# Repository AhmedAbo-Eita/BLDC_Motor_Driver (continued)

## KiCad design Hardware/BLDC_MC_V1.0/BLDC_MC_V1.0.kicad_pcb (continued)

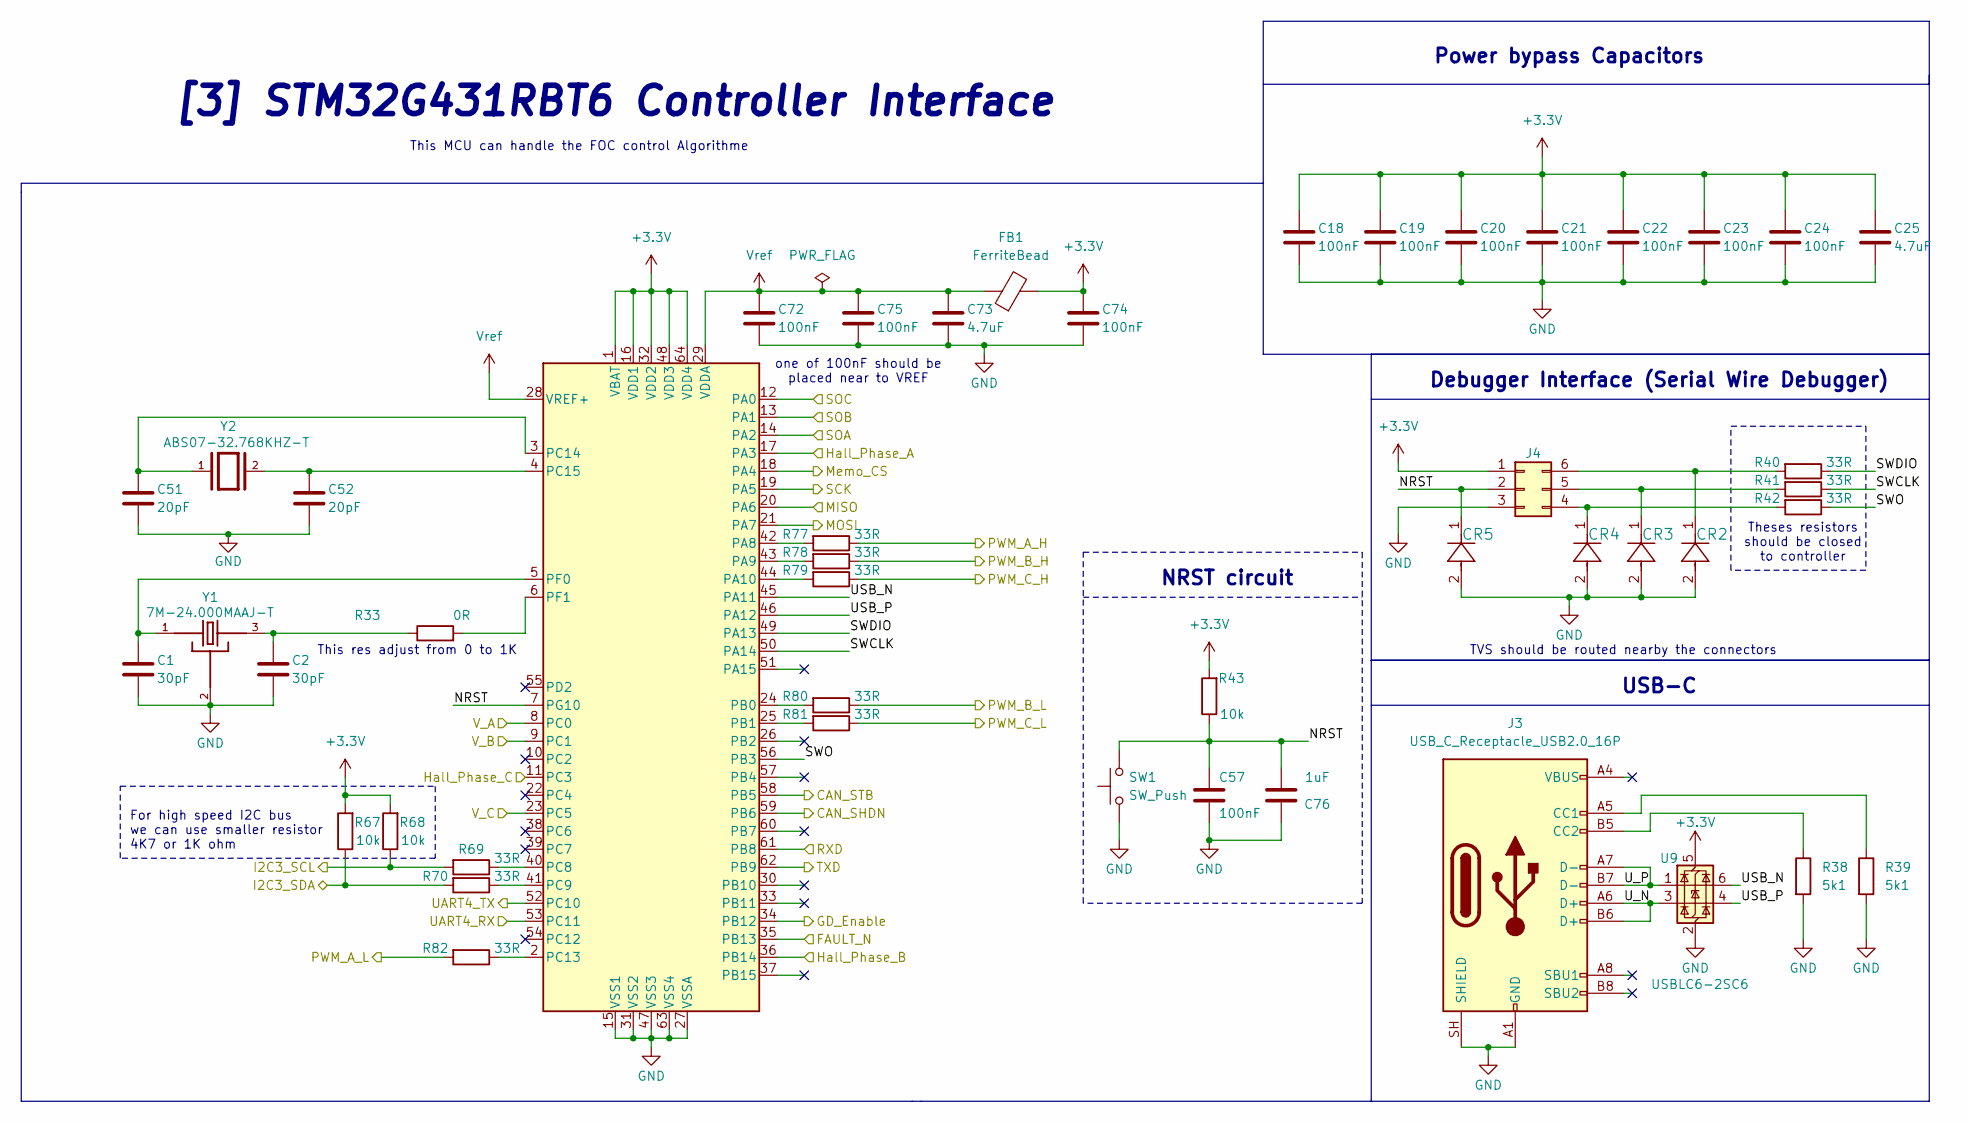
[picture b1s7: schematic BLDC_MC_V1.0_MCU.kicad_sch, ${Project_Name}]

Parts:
C1, C2: 30pF; C_0603_1608Metric; LCSC_PN C113797
C18, C19, C20, C21, C22, C23, C24, C57, C72, C74, C75: 100nF; C_0805_2012Metric; LCSC_PN C28233
C25, C73: 4.7uF; C_1206_3216Metric; LCSC_PN C51205
C51, C52: 20pF; C_0603_1608Metric; LCSC_PN C1648
C76: 1uF; C_0603_1608Metric; LCSC_PN C29936
CR2, CR3, CR4, CR5: PESD3V3L1BA_115; DIODE_PESD3V3L1BA_115_NEX; LCSC_PN C552513
FB1: FerriteBead; L_0603_1608Metric; LCSC_PN C19330
J3: USB_C_Receptacle_USB2.0_16P; USB_C_Receptacle_GCT_USB4105-xx-A_16P_TopMnt_Horizontal
J4: Conn_02x03_Counter_Clockwise; PinHeader_2x03_P2.54mm_Vertical
R33: 0R; R_0603_1608Metric; LCSC_PN C2906974
R38, R39: 5k1; R_0603_1608Metric; LCSC_PN C23186
R40, R41, R42, R69, R70, R77, R78, R79, R80, R81, R82: 33R; R_0603_1608Metric; LCSC_PN C108661
R43: 10k; R_0603_1608Metric; LCSC_PN C98220
R67, R68: 10k; R_0603_1608Metric; LCSC_PN C95204
SW1: SW_Push; SW_Push_1P1T_NO_E-Switch_TL3301NxxxxxG
U4: STM32G431RBT6; LQFP64-10x10mm; LCSC_PN C431633
U9: USBLC6-2SC6; SOT-23-6
Y1: 7M-24.000MAAJ-T; XTAL_7M-24.000MAAJ-T; LCSC_PN C2450233
Y2: ABS07-32.768KHZ-T; XTAL_ABS07-32.768KHZ-T; PARTREV 08.19.15; LCSC_PN C130253

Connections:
+3.3V: C18.1, C19.1, C20.1, C21.1, C22.1, C23.1, C24.1, C25.1, C74.1, FB1.2, J4.1, R43.2, R67.2, R68.2, U4.1 (VBAT), U4.16 (VDD1), U4.32 (VDD2), U4.48 (VDD3), U4.64 (VDD4), U9.5 (VBUS); also elsewhere on the board
/BLDC_MC_V1.0_CAN_Transceiver/CAN_SHDN: U4.59 (PB6); also elsewhere on the board
/BLDC_MC_V1.0_CAN_Transceiver/CAN_STB: U4.58 (PB5); also elsewhere on the board
/BLDC_MC_V1.0_CAN_Transceiver/RXD: U4.61 (PB8); also elsewhere on the board
/BLDC_MC_V1.0_CAN_Transceiver/TXD: U4.62 (PB9); also elsewhere on the board
/BLDC_MC_V1.0_Connectors/I2C3_SCL: R68.1, R69.2; also elsewhere on the board
/BLDC_MC_V1.0_Connectors/I2C3_SDA: R67.1, R70.2; also elsewhere on the board
/BLDC_MC_V1.0_Connectors/UART4_RX: U4.53 (PC11); also elsewhere on the board
/BLDC_MC_V1.0_Connectors/UART4_TX: U4.52 (PC10); also elsewhere on the board
/BLDC_MC_V1.0_Gate_Drive/FAULT_N: U4.35 (PB13); also elsewhere on the board
/BLDC_MC_V1.0_Gate_Drive/GD_Enable: U4.34 (PB12); also elsewhere on the board
/BLDC_MC_V1.0_Gate_Drive/PWM_A_H: R77.1; also elsewhere on the board
/BLDC_MC_V1.0_Gate_Drive/PWM_A_L: R82.2; also elsewhere on the board
/BLDC_MC_V1.0_Gate_Drive/PWM_B_H: R78.1; also elsewhere on the board
/BLDC_MC_V1.0_Gate_Drive/PWM_B_L: R80.1; also elsewhere on the board
/BLDC_MC_V1.0_Gate_Drive/PWM_C_H: R79.1; also elsewhere on the board
/BLDC_MC_V1.0_Gate_Drive/PWM_C_L: R81.1; also elsewhere on the board
/BLDC_MC_V1.0_Gate_Drive/SOA: U4.14 (PA2); also elsewhere on the board
/BLDC_MC_V1.0_Gate_Drive/SOB: U4.13 (PA1); also elsewhere on the board
/BLDC_MC_V1.0_Gate_Drive/SOC: U4.12 (PA0); also elsewhere on the board
/BLDC_MC_V1.0_HallSensor/Hall_Phase_A: U4.17 (PA3); also elsewhere on the board
/BLDC_MC_V1.0_HallSensor/Hall_Phase_B: U4.36 (PB14); also elsewhere on the board
/BLDC_MC_V1.0_HallSensor/Hall_Phase_C: U4.11 (PC3); also elsewhere on the board
/BLDC_MC_V1.0_MCU/MISO: U4.20 (PA6); also elsewhere on the board
/BLDC_MC_V1.0_MCU/MOSI: U4.21 (PA7); also elsewhere on the board
/BLDC_MC_V1.0_MCU/Memo_CS: U4.18 (PA4); also elsewhere on the board
/BLDC_MC_V1.0_MCU/NRST: C57.1, C76.2, CR5.1, J4.2, R43.1, SW1.2, U4.7 (PG10)
/BLDC_MC_V1.0_MCU/SCK: U4.19 (PA5); also elsewhere on the board
/BLDC_MC_V1.0_MCU/SWCLK: R41.1, U4.50 (PA14)
/BLDC_MC_V1.0_MCU/SWDIO: R40.1, U4.49 (PA13)
/BLDC_MC_V1.0_MCU/SWO: R42.1, U4.56 (PB3)
/BLDC_MC_V1.0_MCU/USB_N: U4.45 (PA11), U9.6 (I/O1)
/BLDC_MC_V1.0_MCU/USB_P: U4.46 (PA12), U9.4 (I/O2)
/BLDC_MC_V1.0_MCU/U_N: J3.A6 (D+), J3.B6 (D+), U9.3 (I/O2)
/BLDC_MC_V1.0_MCU/U_P: J3.A7 (D-), J3.B7 (D-), U9.1 (I/O1)
/BLDC_MC_V1.0_MCU/V_A: U4.8 (PC0); also elsewhere on the board
/BLDC_MC_V1.0_MCU/V_B: U4.9 (PC1); also elsewhere on the board
/BLDC_MC_V1.0_MCU/V_C: U4.23 (PC5); also elsewhere on the board
GND: C1.2, C2.2, C18.2, C19.2, C20.2, C21.2, C22.2, C23.2, C24.2, C25.2, C51.2, C52.2, C57.2, C72.2, C73.2, C74.2, C75.2, C76.1, CR2.2, CR3.2, CR4.2, CR5.2, J3.A1 (GND), J3.A12 (GND), J3.SH (SHIELD), J4.3, R38.2, R39.2, SW1.1, U4.15 (VSS1), U4.27 (VSSA), U4.31 (VSS2), U4.47 (VSS3), U4.63 (VSS4), U9.2 (GND), Y1.2, Y1.4; also elsewhere on the board
unnamed: C2.1, R33.1, Y1.3
unnamed: J3.A5 (CC1), R39.1
unnamed: J3.B5 (CC2), R38.1
unnamed: CR4.1, J4.4, R42.2
unnamed: CR3.1, J4.5, R41.2
unnamed: CR2.1, J4.6, R40.2
unnamed: R77.2, U4.42 (PA8)
unnamed: R78.2, U4.43 (PA9)
unnamed: R79.2, U4.44 (PA10)
unnamed: R80.2, U4.24 (PB0)
unnamed: R81.2, U4.25 (PB1)
unnamed: R69.1, U4.40 (PC8)
unnamed: R70.1, U4.41 (PC9)
unnamed: R82.1, U4.2 (PC13)
unnamed: C51.1, U4.3 (PC14), Y2.1
unnamed: C52.1, U4.4 (PC15), Y2.2
unnamed: C1.1, U4.5 (PF0), Y1.1
unnamed: R33.2, U4.6 (PF1)
Vref: C72.1, C73.1, C75.1, FB1.1, U4.28 (VREF+), U4.29 (VDDA); also elsewhere on the board

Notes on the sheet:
Power bypass Capacitors
TVS should be routed nearby the connectors
[3] STM32G431RBT6 Controller Interface
NRST circuit
For high speed I2C bus we can use smaller resistor 4K7 or 1K ohm
Debugger Interface (Serial Wire Debugger)
USB-C
Theses resistors should be closed to controller
This res adjust from 0 to 1K
This MCU can handle the FOC control Algorithme
one of 100nF should be placed near to VREF

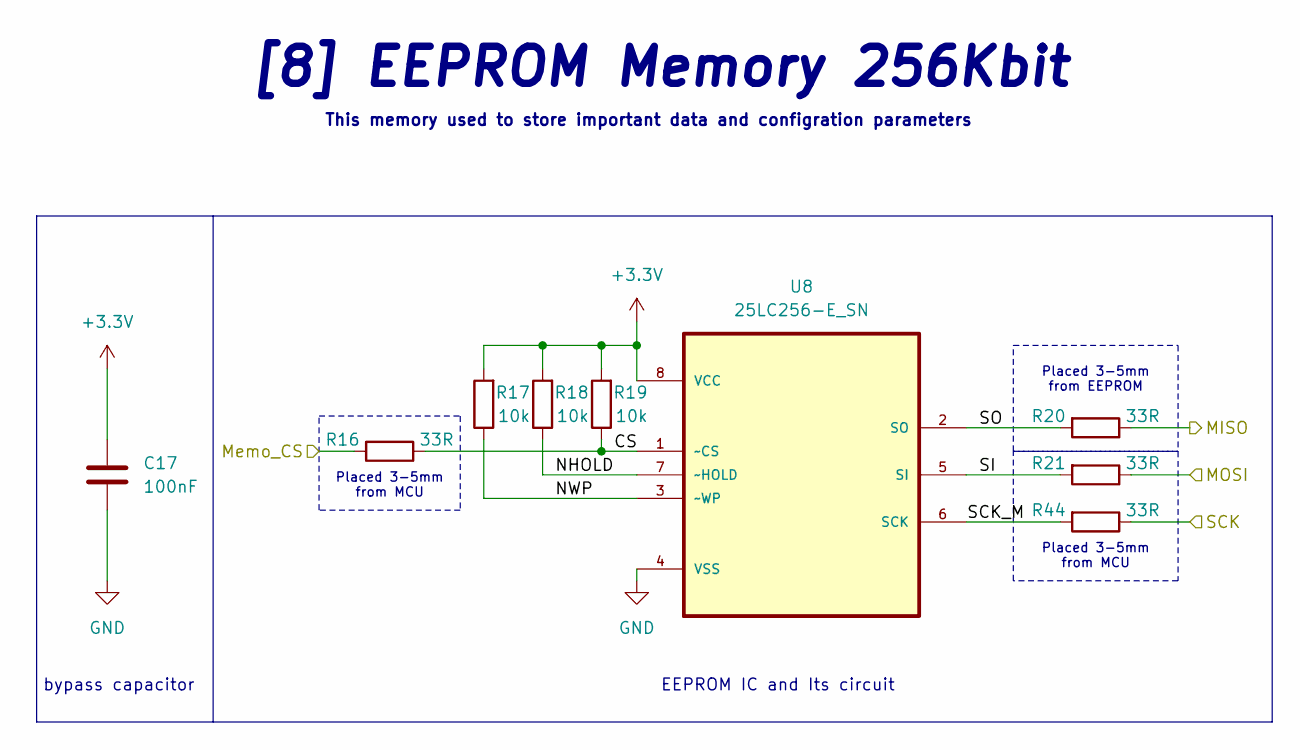
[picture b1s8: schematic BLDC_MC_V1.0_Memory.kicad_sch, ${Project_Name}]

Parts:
C17: 100nF; C_0805_2012Metric; LCSC_PN C28233
R16, R20, R21, R44: 33R; R_0603_1608Metric; LCSC_PN C108661
R17, R18, R19: 10k; R_0603_1608Metric; LCSC_PN C95204
U8: 25LC256-E_SN; SOIC127P599X175-8N; MPN 25LC256-E/SN; LCSC_PN C1349834

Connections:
+3.3V: C17.1, R17.2, R18.2, R19.2, U8.8 (VCC); also elsewhere on the board
/BLDC_MC_V1.0_MCU/MISO: R20.1; also elsewhere on the board
/BLDC_MC_V1.0_MCU/MOSI: R21.1; also elsewhere on the board
/BLDC_MC_V1.0_MCU/Memo_CS: R16.2; also elsewhere on the board
/BLDC_MC_V1.0_MCU/SCK: R44.1; also elsewhere on the board
/BLDC_MC_V1.0_Memory/CS: R16.1, R19.1, U8.1 (~CS)
/BLDC_MC_V1.0_Memory/NHOLD: R18.1, U8.7 (~HOLD)
/BLDC_MC_V1.0_Memory/NWP: R17.1, U8.3 (~WP)
/BLDC_MC_V1.0_Memory/SCK_M: R44.2, U8.6 (SCK)
/BLDC_MC_V1.0_Memory/SI: R21.2, U8.5 (SI)
/BLDC_MC_V1.0_Memory/SO: R20.2, U8.2 (SO)
GND: C17.2, U8.4 (VSS); also elsewhere on the board

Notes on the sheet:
Placed 3-5mm from EEPROM
Placed 3-5mm from MCU
EEPROM IC and Its circuit
This memory used to store important data and configration parameters
bypass capacitor
[8] EEPROM Memory 256Kbit

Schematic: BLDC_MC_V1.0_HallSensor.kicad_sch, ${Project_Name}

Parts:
C58, C59, C60: C; C_0603_1608Metric
C61, C62, C63: 100nF; C_0805_2012Metric; LCSC_PN C28233
R15, R49, R52: 10k; R_0603_1608Metric; LCSC_PN C95204
R45, R47, R50: 18K; R_0603_1608Metric; LCSC_PN C309650
R46, R48, R51: 30K; R_0603_1608Metric; LCSC_PN C723585
U3, U10, U11: TLV9061IDBVR; SOT95P280X145-5N; LCSC_PN C398358

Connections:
+3.3V: C61.1, C62.1, C63.1, U3.5 (V+), U10.5 (V+), U11.5 (V+); also elsewhere on the board
/BLDC_MC_V1.0_Connectors/Hall_A: R45.2; also elsewhere on the board
/BLDC_MC_V1.0_Connectors/Hall_B: R47.2; also elsewhere on the board
/BLDC_MC_V1.0_Connectors/Hall_C: R50.2; also elsewhere on the board
/BLDC_MC_V1.0_HallSensor/Hall_Phase_A: U3.1 (OUT), U3.4 (IN-); also elsewhere on the board
/BLDC_MC_V1.0_HallSensor/Hall_Phase_B: U10.1 (OUT), U10.4 (IN-); also elsewhere on the board
/BLDC_MC_V1.0_HallSensor/Hall_Phase_C: U11.1 (OUT), U11.4 (IN-); also elsewhere on the board
GND: C58.2, C59.2, C60.2, C61.2, C62.2, C63.2, R46.2, R48.2, R51.2, U3.2 (V-), U10.2 (V-), U11.2 (V-); also elsewhere on the board
unnamed: C58.1, R15.1, R45.1, R46.1
unnamed: C59.1, R47.1, R48.1, R49.1
unnamed: C60.1, R50.1, R51.1, R52.1
unnamed: R15.2, U3.3 (IN+)
unnamed: R49.2, U10.3 (IN+)
unnamed: R52.2, U11.3 (IN+)

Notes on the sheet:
For filtering the signal Limiting the input current
[6] Hall Effect Sensor Interface
+3.125V
Drop down the voltage from 5 to 3.3V
For the 3 Phases of Hall Sensor
Buffer OpAmp

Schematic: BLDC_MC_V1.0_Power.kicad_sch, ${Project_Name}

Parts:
C3, C4, C7, C8, C31, C35, C54, C89, C90: 100nF; C_0805_2012Metric; LCSC_PN C28233
C5, C6, C26, C27: 47uF; C_1206_3216Metric; LCSC_PN C403725
C9, C10, C29, C30: 47uF; CP_Elec_10x10.5; LCSC_PN C46528101
C14: 10nF; C_1206_3216Metric; LCSC_PN C377055
C28: 10pF; C_0603_1608Metric; LCSC_PN C1634
C32: 470nF; C_0805_2012Metric; LCSC_PN C13967
C33: 10nF; C_0603_1608Metric; LCSC_PN C100042
C34: 2.2uF; C_0603_1608Metric; LCSC_PN C415535
C36, C53: 1uF; C_0805_2012Metric; LCSC_PN C28323
C37, C55, C56: 4.7uF; C_1206_3216Metric; LCSC_PN C51205
CR10: SMDJ110CA; SMDJSeries_LTF; LCSC_PN C2990268
D1, D2, D3, D4: LED; LED_0603_1608Metric; LCSC_PN C19171390
H1, H2, H3, H4: MountingHole_Pad; MountingHole_2.2mm_M2_Pad_Via
L1: 10uH; L_KOHERelec_MDA7030; LCSC_PN C149584
NT4: NetTie_2; NetTie-2_SMD_Pad2.0mm
Q7: BSC027N10NS5ATMA1; PG-TSON-8-3_INF; PARTREV 2.1; LCSC_PN C534315
R1, R2: 100K; R_0603_1608Metric; LCSC_PN C122538
R3, R6: 0R; R_0603_1608Metric; LCSC_PN C2906974
R4: 9.09K; R_0603_1608Metric; LCSC_PN C844591
R5, R34, R37: 10k; R_0603_1608Metric; LCSC_PN C98220
R9: 1MR; R_1206_3216Metric; LCSC_PN C2907441
R35, R36: 3k3; R_0603_1608Metric; LCSC_PN C22978
U1: LM76005RNPR; QFN50P600X400X80-31N; PARTREV A; LCSC_PN TI LM76005RNPR
U5: LDL1117S33R; SOT230P700X180-4N; PARTREV 7; LCSC_PN C435835
U7: NCV4274ADT50RKG; DPAK-3_ONS; LCSC_PN C233416
U16: LM74700QDRQ1; SOIC8_D_TEX; LCSC_PN C33579657

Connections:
+3.3V: C35.1, C37.1, R36.1, U5.2 (VOUT), U5.4 (VOUT); also elsewhere on the board
+5V: C55.1, C56.1, R35.1, U7.3 (Q); also elsewhere on the board
+12V: C3.1, C4.1, C5.2, C6.2, C26.2, C27.2, C28.1, C36.1, C53.1, C54.1, L1.2, R2.1, R5.2, R6.2, R34.1, U5.3 (VIN), U7.1 (I); also elsewhere on the board
/BLDC_MC_V1.0_Connectors/Vin_DC: C89.1, C90.1, CR10.1, Q7.5, Q7.6, Q7.7, Q7.8, U16.2 (EN), U16.5 (ANODE); also elsewhere on the board
/BLDC_MC_V1.0_Power/Buck_SW: C32.1, L1.1, U1.1 (SW), U1.2 (SW), U1.3 (SW), U1.4 (SW), U1.5 (SW)
/BLDC_MC_V1.0_Power/VCC_Buck: C34.1, U1.8 (VCC)
/BLDC_MC_V1.0_Power/chassis_ground: C14.1, H1.1 (1_1), H2.1 (1_1), H3.1 (1_1), H4.1 (1_1), R9.1
AGND: C31.2, C33.2, C34.2, NT4.2, R1.2, R3.2, R4.2, U1.13 (AGND), U1.14 (AGND), U1.15 (AGND), U1.19 (NC), U1.27 (NC), U1.28 (NC), U1.29 (NC), U1.30 (NC)
GND: C3.2, C4.2, C5.1, C6.1, C7.2, C8.2, C9.2, C10.2, C14.2, C26.1, C27.1, C29.2, C30.2, C35.2, C36.2, C37.2, C53.2, C54.2, C55.2, C56.2, C90.2, CR10.2, D1.1 (K), D2.1 (K), D3.1 (K), D4.1 (K), NT4.1, R9.2, U1.24 (GND), U1.25 (GND), U1.26 (GND), U1.31 (EP), U5.1 (GND), U7.2 (GND), U16.1 (GND); also elsewhere on the board
unnamed: D1.2 (A), R37.2
unnamed: D2.2 (A), R34.2
unnamed: D3.2 (A), R35.2
unnamed: D4.2 (A), R36.2
unnamed: C31.1, R6.1, U1.9 (BIAS)
unnamed: C32.2, U1.6 (BOOT)
unnamed: C28.2, R2.2, R4.1, U1.12 (FB)
unnamed: R5.1, U1.16 (PGOOD)
unnamed: R1.1, U1.10 (RT)
unnamed: C33.1, U1.11 (SS/TRK)
unnamed: R3.1, U1.17 (SYNC/MODE)
unnamed: Q7.4, U16.6 (GATE)
unnamed: U16.3 (N.C), U16.7 (N.C)
unnamed: C89.2, U16.4 (VCAP)
Vin: C7.1, C8.1, C9.1, C10.1, C29.1, C30.1, Q7.1, Q7.2, Q7.3, R37.1, U1.18 (EN), U1.20 (PVIN), U1.21 (PVIN), U1.22 (PVIN), U16.8 (CATHODE); also elsewhere on the board

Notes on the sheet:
Input Cap Bank
Output Cap Bank
The maximum input votage of this 60V so we can use for BLDC motors up to 60V
LDO Fixed out 5V
Indication Leds
Buck IC Circuit
input Capacitor Bank To make the input power pure DC
LDO Fixed out 3.3V
Input PWR Protection
Replaced by 0R
[1] Power Conversion Vin to 12V and 5V to 3.3V
Output Capacitor Bank Recommended from IC datasheet Cout = 150uf Referance design puts 5 of 47uf

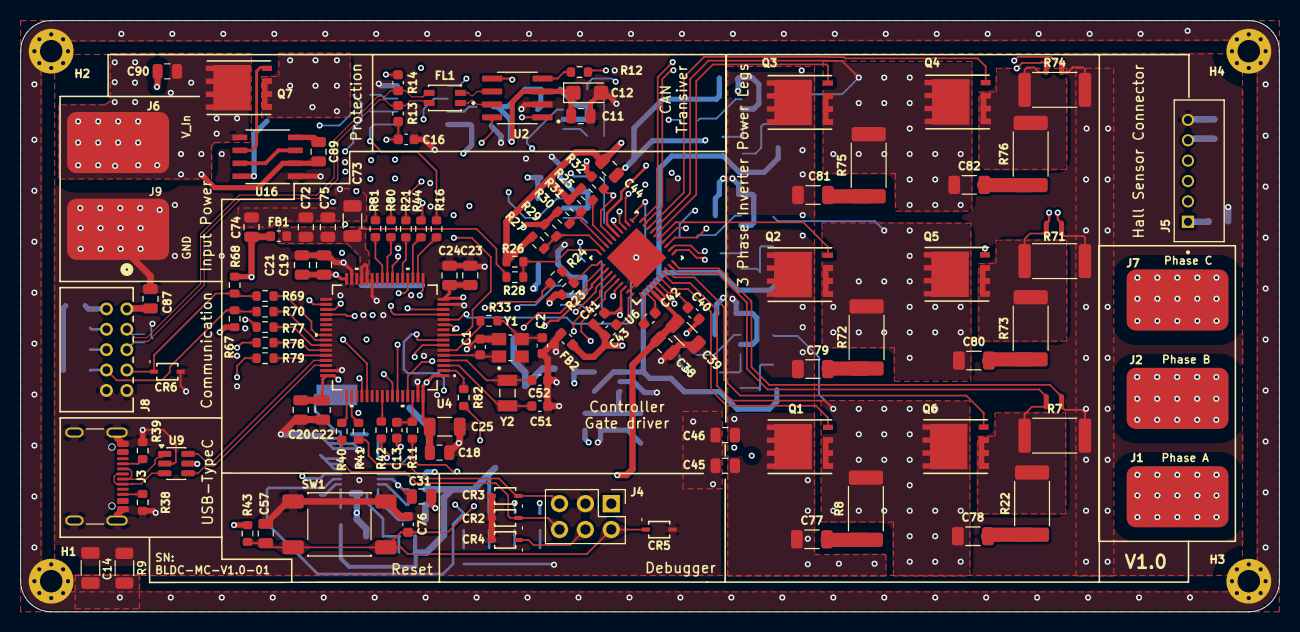
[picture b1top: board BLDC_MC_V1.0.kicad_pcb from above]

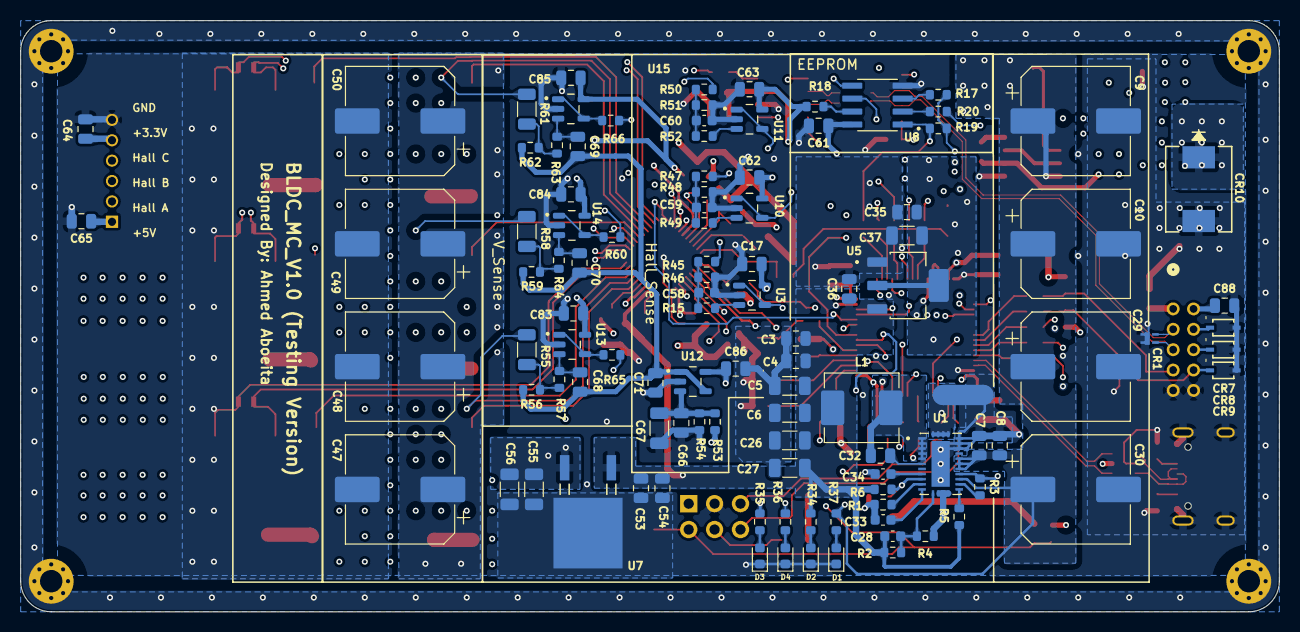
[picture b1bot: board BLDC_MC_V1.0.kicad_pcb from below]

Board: 8 copper layers, 123.5 x 58.0 mm, 234 parts (106 on the bottom side), 148 nets.

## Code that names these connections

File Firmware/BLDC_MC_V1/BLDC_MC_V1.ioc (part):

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Mcu.Name=STM32G431R(6-8-B)Tx
Mcu.Package=LQFP64
Mcu.UserName=STM32G431RBTx
PA0.Mode=IN1-Single-Ended
PA0.Signal=ADC1_IN1
PA1.Mode=IN2-Single-Ended
PA1.Signal=ADC1_IN2
PA10.Signal=S_TIM1_CH3
PA11.Mode=Device
PA11.Signal=USB_DM
PA12.Mode=Device
PA12.Signal=USB_DP
PA13.Mode=Trace_Asynchronous_SW
PA13.Signal=SYS_JTMS-SWDIO
PA14.Mode=Trace_Asynchronous_SW
PA14.Signal=SYS_JTCK-SWCLK
PA2.Mode=IN3-Single-Ended
PA2.Signal=ADC1_IN3
PA3.Mode=IN4-Single-Ended
PA3.Signal=ADC1_IN4
PA4.Signal=GPIO_Output
PA5.Mode=Full_Duplex_Master
PA5.Signal=SPI1_SCK
PA6.Mode=Full_Duplex_Master
PA6.Signal=SPI1_MISO
PA7.Mode=Full_Duplex_Master
PA7.Signal=SPI1_MOSI
PA8.Signal=S_TIM1_CH1
PA9.Signal=S_TIM1_CH2
PB0.Mode=PWM Generation2 CH2 CH2N
PB0.Signal=TIM1_CH2N
PB1.Mode=Output Compare3 CH3 CH3N
PB1.Signal=TIM1_CH3N
PB12.Signal=GPIO_Output
PB13.Signal=GPIO_Input
PB14.Mode=IN5-Single-Ended
PB14.Signal=ADC1_IN5
PB3.Mode=Trace_Asynchronous_SW
PB3.Signal=SYS_JTDO-SWO
PB5.Signal=GPIO_Output
PB6.Signal=GPIO_Output
PB7.Mode=Mode_PVD_Ext
PB7.Signal=SYS_PVD_IN
PB8-BOOT0.Mode=FDCAN_Activate
PB8-BOOT0.Signal=FDCAN1_RX
PB9.Mode=FDCAN_Activate
PB9.Signal=FDCAN1_TX
PC0.Mode=IN6-Single-Ended
PC0.Signal=ADC1_IN6
PC1.Mode=IN7-Single-Ended
PC1.Signal=ADC1_IN7
PC10.Mode=Asynchronous
PC10.Signal=UART4_TX
PC11.Mode=Asynchronous
PC11.Signal=UART4_RX
PC13.Mode=Output Compare1 CH1 CH1N
PC13.Signal=TIM1_CH1N
PC14-OSC32_IN.Mode=LSE-External-Oscillator
PC14-OSC32_IN.Signal=RCC_OSC32_IN
PC15-OSC32_OUT.Mode=LSE-External-Oscillator
PC15-OSC32_OUT.Signal=RCC_OSC32_OUT
PC2.Mode=IN8-Single-Ended
PC2.Signal=ADC1_IN8
PC5.Mode=IN11-Single-Ended
PC5.Signal=ADC2_IN11
PC8.Mode=I2C
PC8.Signal=I2C3_SCL
PC9.Mode=I2C
PC9.Signal=I2C3_SDA
PF0-OSC_IN.Mode=HSE-External-Oscillator
PF0-OSC_IN.Signal=RCC_OSC_IN
PF1-OSC_OUT.Mode=HSE-External-Oscillator
PF1-OSC_OUT.Signal=RCC_OSC_OUT
RCC.HSE_VALUE=24000000
RCC.SYSCLKFreq_VALUE=168000000
RCC.SYSCLKSource=RCC_SYSCLKSOURCE_PLLCLK
board=custom

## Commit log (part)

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2025-12-20 Add BLDC_Motor_Driver Kicad Project
2025-12-20 add power and MCU sub sheets
2026-01-03 Add buck converter IC 36V input to 3.3V
2026-01-04 started the MCU and Finializing the MCU the next step will be the DRV
2026-01-05 Add Selection of CAN IC and arrange the sheet of buck converter
2026-01-05 Complete CAN IC sheet
2026-01-07 Add the datasheet of EEPROM Memory
2026-01-07 Add the Library of EEPROM
2026-01-07 Edit the value of series resistor to 33R instead of 49.9R
2026-01-07 Add the EEPROM memory sheet and finish the circuit of it
2026-01-07 add CS series resistor to EEPROM Schematic
2026-01-07 Add the MOSFET for the 3 phase inverter sheet
2026-01-09 Rename the project files to take version name
2026-01-09 Remove buckups
2026-01-10 Add edits to the datasheet of buck converter
2026-01-10 Add the datasheet of LDO used to generate 3.3V for MCU, CAN and memory
2026-01-10 Add the library of LDO and New buck converter
2026-01-10 add the new edits to Buck converter sheet and edit other sheets name
2026-01-12 Remove project old sheets
2026-01-12 Add datasheet and library of DVR (gate drive IC) and add the sheet of gate drive circuit
2026-01-25 Edit the connection between sheets and add some details and connections to gatedrive sheet
2026-02-02 Restore the importenat project files from last commit and define the routing of current sensor as differntial pair
2026-02-07 Add CAN bus Chake
2026-02-07 Edit project confg
2026-02-07 add simulation files
2026-02-07 edit ignore file
2026-02-08 Edit Controller sheet and add oscillators for the controller
2026-02-08 Remove STM project
2026-02-08 Add STM project
2026-02-13 Add LDO 5V library
2026-02-13 Edit the ground of the capacitors to PGND
2026-02-13 Add 5V LDO
2026-02-13 Edit main sheet (root)
2026-02-13 Edit FW project using external oscillator and confg of PWM
2026-02-21 Add the configration of PWM pins to the project and add interfacing pins with gate driver
2026-02-21 Add the USB-C connector - define the PWM pins and other enable and fault pins for gate driver
2026-02-22 Add snubber circuit and edit pages numbers
2026-02-28 Add the JTAG debug interface
2026-03-01 Add TVS for NRST and add pushbutton for rest
2026-03-02 Edit the project with the pins selected in HW
2026-03-02 Add the new bipolar TVS for the debugger connector
2026-03-04 Add hall sensor sheet and its simulation file
2026-03-04 Update the pinout with 3 ADC pins for Hall Sensor
2026-03-04 Add the Datasheet and the component library of TLV9061IDBVR OpAmp used in Hall Sensor Circuit
2026-03-04 Add the simulation files for the hall sensor interacing circuit
2026-03-04 Edit the sch of the project by adding the hall sensor sheet and interface with the MCU sheet and annotate the components in memory sheet
2026-03-06 Add voltage sensor to measure the 3 phase voltage of inverter bridge
2026-03-07 Add simulation files for the voltage sensor of 3 phase
2026-03-08 Update the project Pinout - Add I2C and UART interface
2026-03-08 Add the snubber circuit and arrange the sheet
2026-03-08 Add connectors sheet
2026-03-08 Add space in the power sheet for input power ( reverce polarity and over current protection )
2026-03-08 Edit the voltage sensor sheet by adding low pass filter
2026-03-08 Edit the controller sheet and CAN sheet to adjust the interface between them
2026-03-11 Add bypass capacitors for the OpAmps
2026-03-14 Add connectors library (symbol, footprint and 3D model)
2026-03-14 Adjust the connections between sheets
2026-03-14 Add the connectors used in the project ( power, sensor and communication connectors)
2026-03-16 Add TVS protection for communication connector
2026-03-17 Add SCH PDF
2026-03-20 Add in series resistors for PWM pins and Test points for the same pins
2026-03-20 Add test points for the gate drive pins
2026-03-22 Edit the libraries of the project
2026-03-22 Add the data sheet of reverse polarity controller IC
2026-03-22 Edit some libraries to solve errors of SCH
2026-03-22 Solve all errors and wornings in project
2026-03-22 Update the SCH regarding the last updates 23/3/2026
2026-03-28 Add notes about how to adjust the snubber circuit
2026-03-28 Run DRC and solve all errors and warnings (project updated to Kicad 10)
2026-04-13 Add Control Modeling for the BLDC
2026-06-19 Update recovery files of the project
2026-06-23 Update the plaacement of PCB
2026-06-24 Update the placement of the PCB
2026-06-24 Update the placement of the board
2026-06-26 Add Files of Power and Communication connectors
2026-06-26 Update the component placement of the board
2026-06-27 Update the connector pins as passive
2026-06-27 Update the components' placement of the board
2026-06-28 Add Stackup for the PCB and define the control impedance traces
2026-06-29 Routing Power plans and change the power connedtors
